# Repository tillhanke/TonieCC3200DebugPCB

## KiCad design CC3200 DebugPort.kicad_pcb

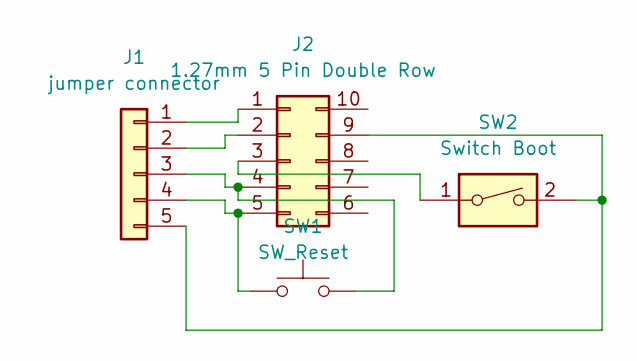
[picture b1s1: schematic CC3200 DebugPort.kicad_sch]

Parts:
J1: jumper connector; PinHeader_1x05_P2.54mm_Vertical
J2: 1.27mm 5 Pin Double Row; PinHeader_2x05_P1.27mm_Vertical
SW1: SW_Reset; SW_PUSH_6mm_H4.3mm
SW2: Switch Boot; SW_DIP_SPSTx01_Slide_9.78x4.72mm_W7.62mm_P2.54mm

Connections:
unnamed: J1.1, J2.1
unnamed: J1.2, J2.2
unnamed: J1.3, J2.4, SW1.2
unnamed: J1.4, J2.5, SW1.1
unnamed: J1.5, J2.9, SW2.2
unnamed: J2.3, SW2.1

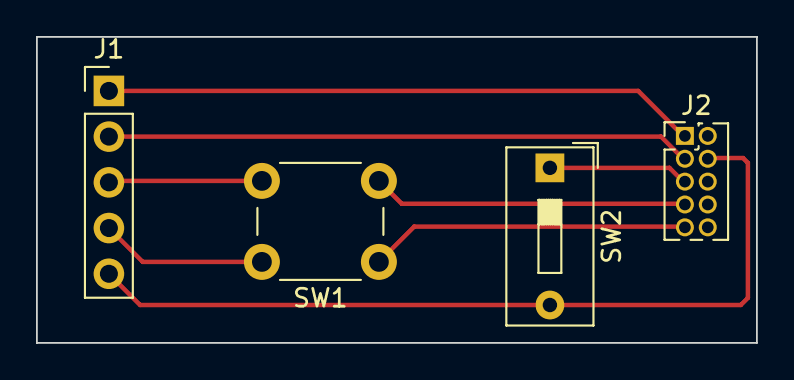
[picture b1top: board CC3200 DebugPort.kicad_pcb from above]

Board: 2 copper layers, 40.0 x 17.0 mm, 4 parts (0 on the bottom side), 6 nets.
